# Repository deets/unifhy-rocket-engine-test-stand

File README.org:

* UNIFHY - universeller Prüfstand für Feststoff- und Hybridmotoren

Ziel dieses Projektes ist die Entwicklung eines preiswerten
Prüfstandes mit einem Preis von maximal 500 EUR.

Der Prüfstand besteht aus drei Modulen:

 - Modul 1: einem aus ITEM Prüfbalken bestehenden mechanischen Aufbau.
 - Modul 2: einer Prüfbox zur Datenaufnahme, Speicherung, Übermittlung und
   gegebenenfalls Fernsteuerung.
 - Modul 3: einer Software zur Konfiguration, Datenerfassung und Auswertung von Modul 2.

Hier die [[file:doc/Pruefstand_UNIFHY.pdf][Anforderungen erhoben am 22.02.2020]].

** Modul 1 - Teststand

Ein Aufbau des Testands von Andreas:

[[./doc/Teststand-Totale.jpg]]

[[./doc/Hybrid-Haengend.jpg]]

[[./doc/Test-mit-laufendem-Motor.jpg]]

** Modul 2 - Firmware

*** ADS1256 Breakout Board

Pin out of the breakout board as seen from top with control interface
to the left:

|-----+----------+---------|
| Pin | Function | P2 Eval |
|-----+----------+---------|
|   1 | PDWN     |      21 |
|   2 | CS_      |      20 |
|   3 | DRDY     |      19 |
|   4 | DOUT     |      17 |
|   5 | DIN      |      18 |
|   6 | SCLK     |      16 |
|   7 | GND      |     GND |
|   8 | 5V       |     EXT |
|-----+----------+---------|

#+attr_html: :width 400 px
[[file:doc/ads1256-breakout.jpg]]

** GIT Konfiguration

Wir arbeiten mit einem [[https://medium.com/singlestone/a-git-workflow-using-rebase-1b1210de83e5][rebase]] basierten GIT workflow. Dazu ist es
hilfreich eine Reihe von Einstellungen vorzunehmen. Die folgenden
Kommandos werden in einer Shell eingegeben, und man muss sich in
der Arbeitskopie befinden:

#+begin_src bash
git config pull.rebase true
#+end_src

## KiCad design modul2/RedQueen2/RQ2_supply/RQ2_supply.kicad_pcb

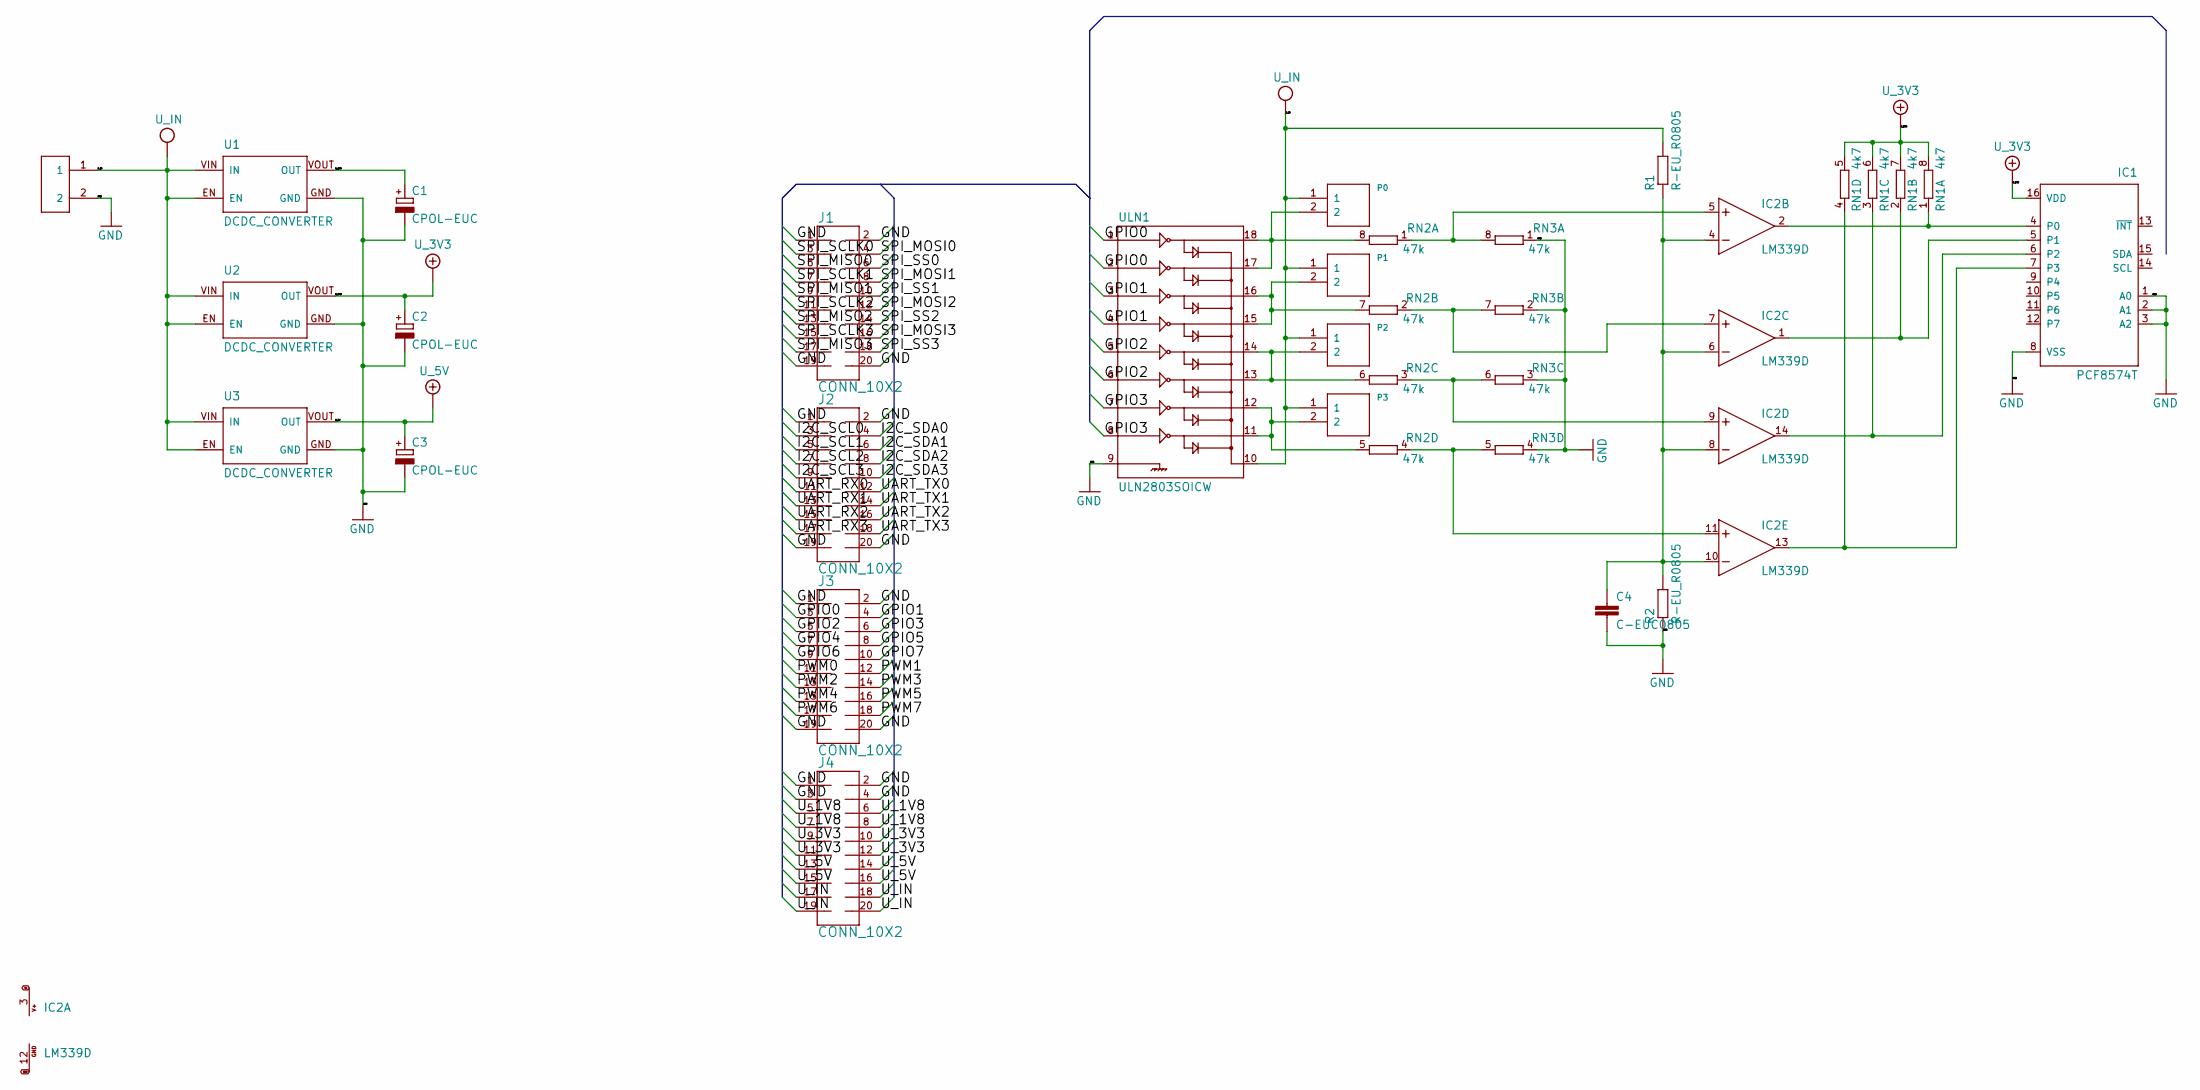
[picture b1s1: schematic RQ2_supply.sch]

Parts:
C1, C2, C3: CPOL-EUC; PANASONIC_C
C4: C-EUC0805; C0805
IC1: PCF8574T; SO16W
IC2: LM339D; SO14
J1, J2, J3, J4: CONN_10X2; 2X10
P0, P1, P2, P3: 2PIN; B2B-PH-K-S
R1, R2: R-EU_R0805; R0805
RN1: 4k7; 0603-ARV
RN2, RN3: 47k; 0603-ARV
U1, U2, U3: DCDC_CONVERTER
U$1: XT_CONN; XT30_PCB
ULN1: ULN2803SOICW; SO18L

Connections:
/GPIO0: J3.3, ULN1.1, ULN1.2
/GPIO1: J3.4, ULN1.3, ULN1.4
/GPIO2: J3.5, ULN1.5, ULN1.6
/GPIO3: J3.6, ULN1.7, ULN1.8
/GPIO4: J3.7
/GPIO5: J3.8
/GPIO6: J3.9
/GPIO7: J3.10
/I2C_SCL0: J2.3
/I2C_SCL1: J2.5
/I2C_SCL2: J2.7
/I2C_SCL3: J2.9
/I2C_SDA0: J2.4
/I2C_SDA1: J2.6
/I2C_SDA2: J2.8
/I2C_SDA3: J2.10
/PWM0: J3.11
/PWM1: J3.12
/PWM2: J3.13
/PWM3: J3.14
/PWM4: J3.15
/PWM5: J3.16
/PWM6: J3.17
/PWM7: J3.18
/SPI_MISO0: J1.5
/SPI_MISO1: J1.9
/SPI_MISO2: J1.13
/SPI_MISO3: J1.17
/SPI_MOSI0: J1.4
/SPI_MOSI1: J1.8
/SPI_MOSI2: J1.12
/SPI_MOSI3: J1.16
/SPI_SCLK0: J1.3
/SPI_SCLK1: J1.7
/SPI_SCLK2: J1.11
/SPI_SCLK3: J1.15
/SPI_SS0: J1.6
/SPI_SS1: J1.10
/SPI_SS2: J1.14
/SPI_SS3: J1.18
/UART_RX0: J2.11
/UART_RX1: J2.13
/UART_RX2: J2.15
/UART_RX3: J2.17
/UART_TX0: J2.12
/UART_TX1: J2.14
/UART_TX2: J2.16
/UART_TX3: J2.18
/U_1V8: C1.+, J4.5, J4.6, J4.7, J4.8, U1.VOUT (OUT)
GND: C1.-, C2.-, C3.-, C4.2, IC1.1 (A0), IC1.2 (A1), IC1.3 (A2), IC1.8 (VSS), IC2.12 (GND), J1.1, J1.2, J1.19, J1.20, J2.1, J2.2, J2.19, J2.20, J3.1, J3.2, J3.19, J3.20, J4.1, J4.2, J4.3, J4.4, R2.1, RN3.1, RN3.2 (1), RN3.3 (1), RN3.4 (1), U1.GND, U2.GND, U3.GND, U$1.2, ULN1.9
unnamed: C4.1, IC2.4 (-IN), IC2.6 (-IN), IC2.8 (-IN), IC2.10 (-IN), R1.1, R2.2
unnamed: IC1.4 (P0), IC2.2 (OUT), RN1.1
unnamed: IC1.5 (P1), IC2.1 (OUT), RN1.2 (1)
unnamed: IC1.6 (P2), IC2.14 (OUT), RN1.3 (1)
unnamed: IC1.7 (P3), IC2.13 (OUT), RN1.4 (1)
unnamed: IC2.5 (+IN), RN2.1, RN3.8 (2)
unnamed: IC2.7 (+IN), RN2.2 (1), RN3.7 (2)
unnamed: IC2.9 (+IN), RN2.3 (1), RN3.6 (2)
unnamed: IC2.11 (+IN), RN2.4 (1), RN3.5 (2)
unnamed: P0.2, RN2.8 (2), ULN1.17, ULN1.18
unnamed: P1.2, RN2.7 (2), ULN1.15, ULN1.16
unnamed: P2.2, RN2.6 (2), ULN1.13, ULN1.14
unnamed: P3.2, RN2.5 (2), ULN1.11, ULN1.12
U_3V3: C2.+, IC1.16 (VDD), J4.9, J4.10, J4.11, J4.12, RN1.5 (2), RN1.6 (2), RN1.7 (2), RN1.8 (2), U2.VOUT (OUT)
U_5V: C3.+, J4.13, J4.14, J4.15, J4.16, U3.VOUT (OUT)
U_IN: J4.17, J4.18, J4.19, J4.20, P0.1, P1.1, P2.1, P3.1, R1.2, U1.EN, U1.VIN (IN), U2.EN, U2.VIN (IN), U3.EN, U3.VIN (IN), U$1.1, ULN1.10
V+: IC2.3 (V+)

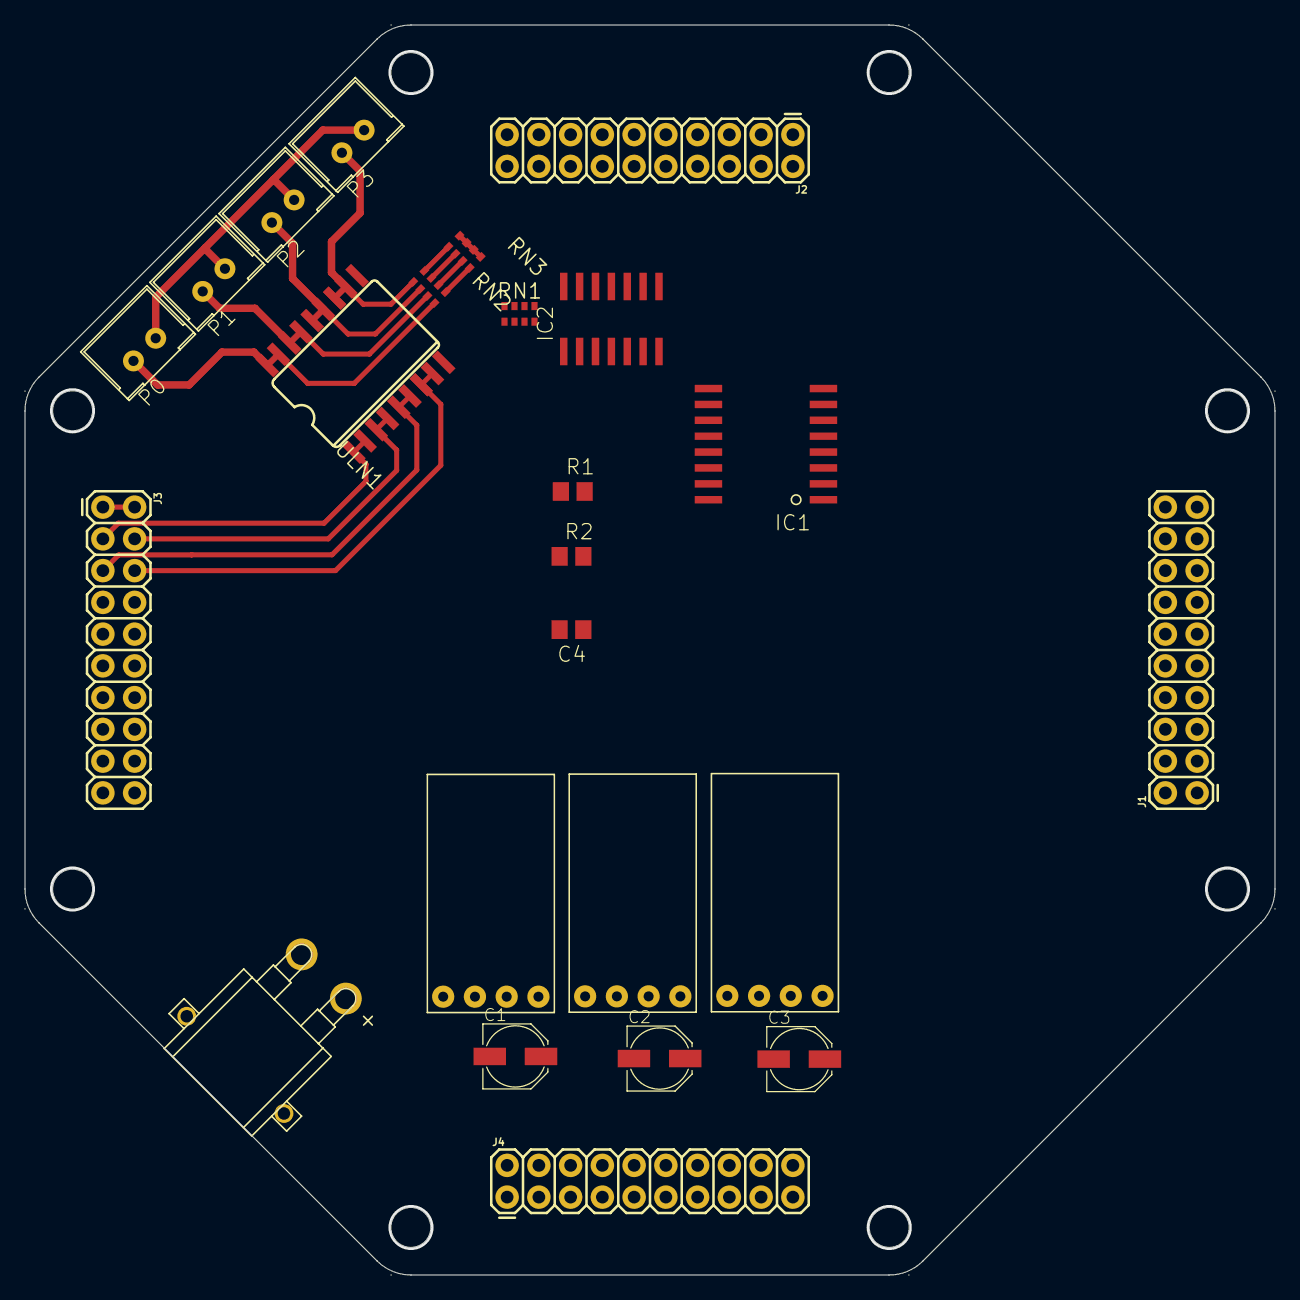
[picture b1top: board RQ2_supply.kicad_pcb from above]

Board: 2 copper layers, 100.0 x 100.0 mm, 24 parts (0 on the bottom side), 22 nets.

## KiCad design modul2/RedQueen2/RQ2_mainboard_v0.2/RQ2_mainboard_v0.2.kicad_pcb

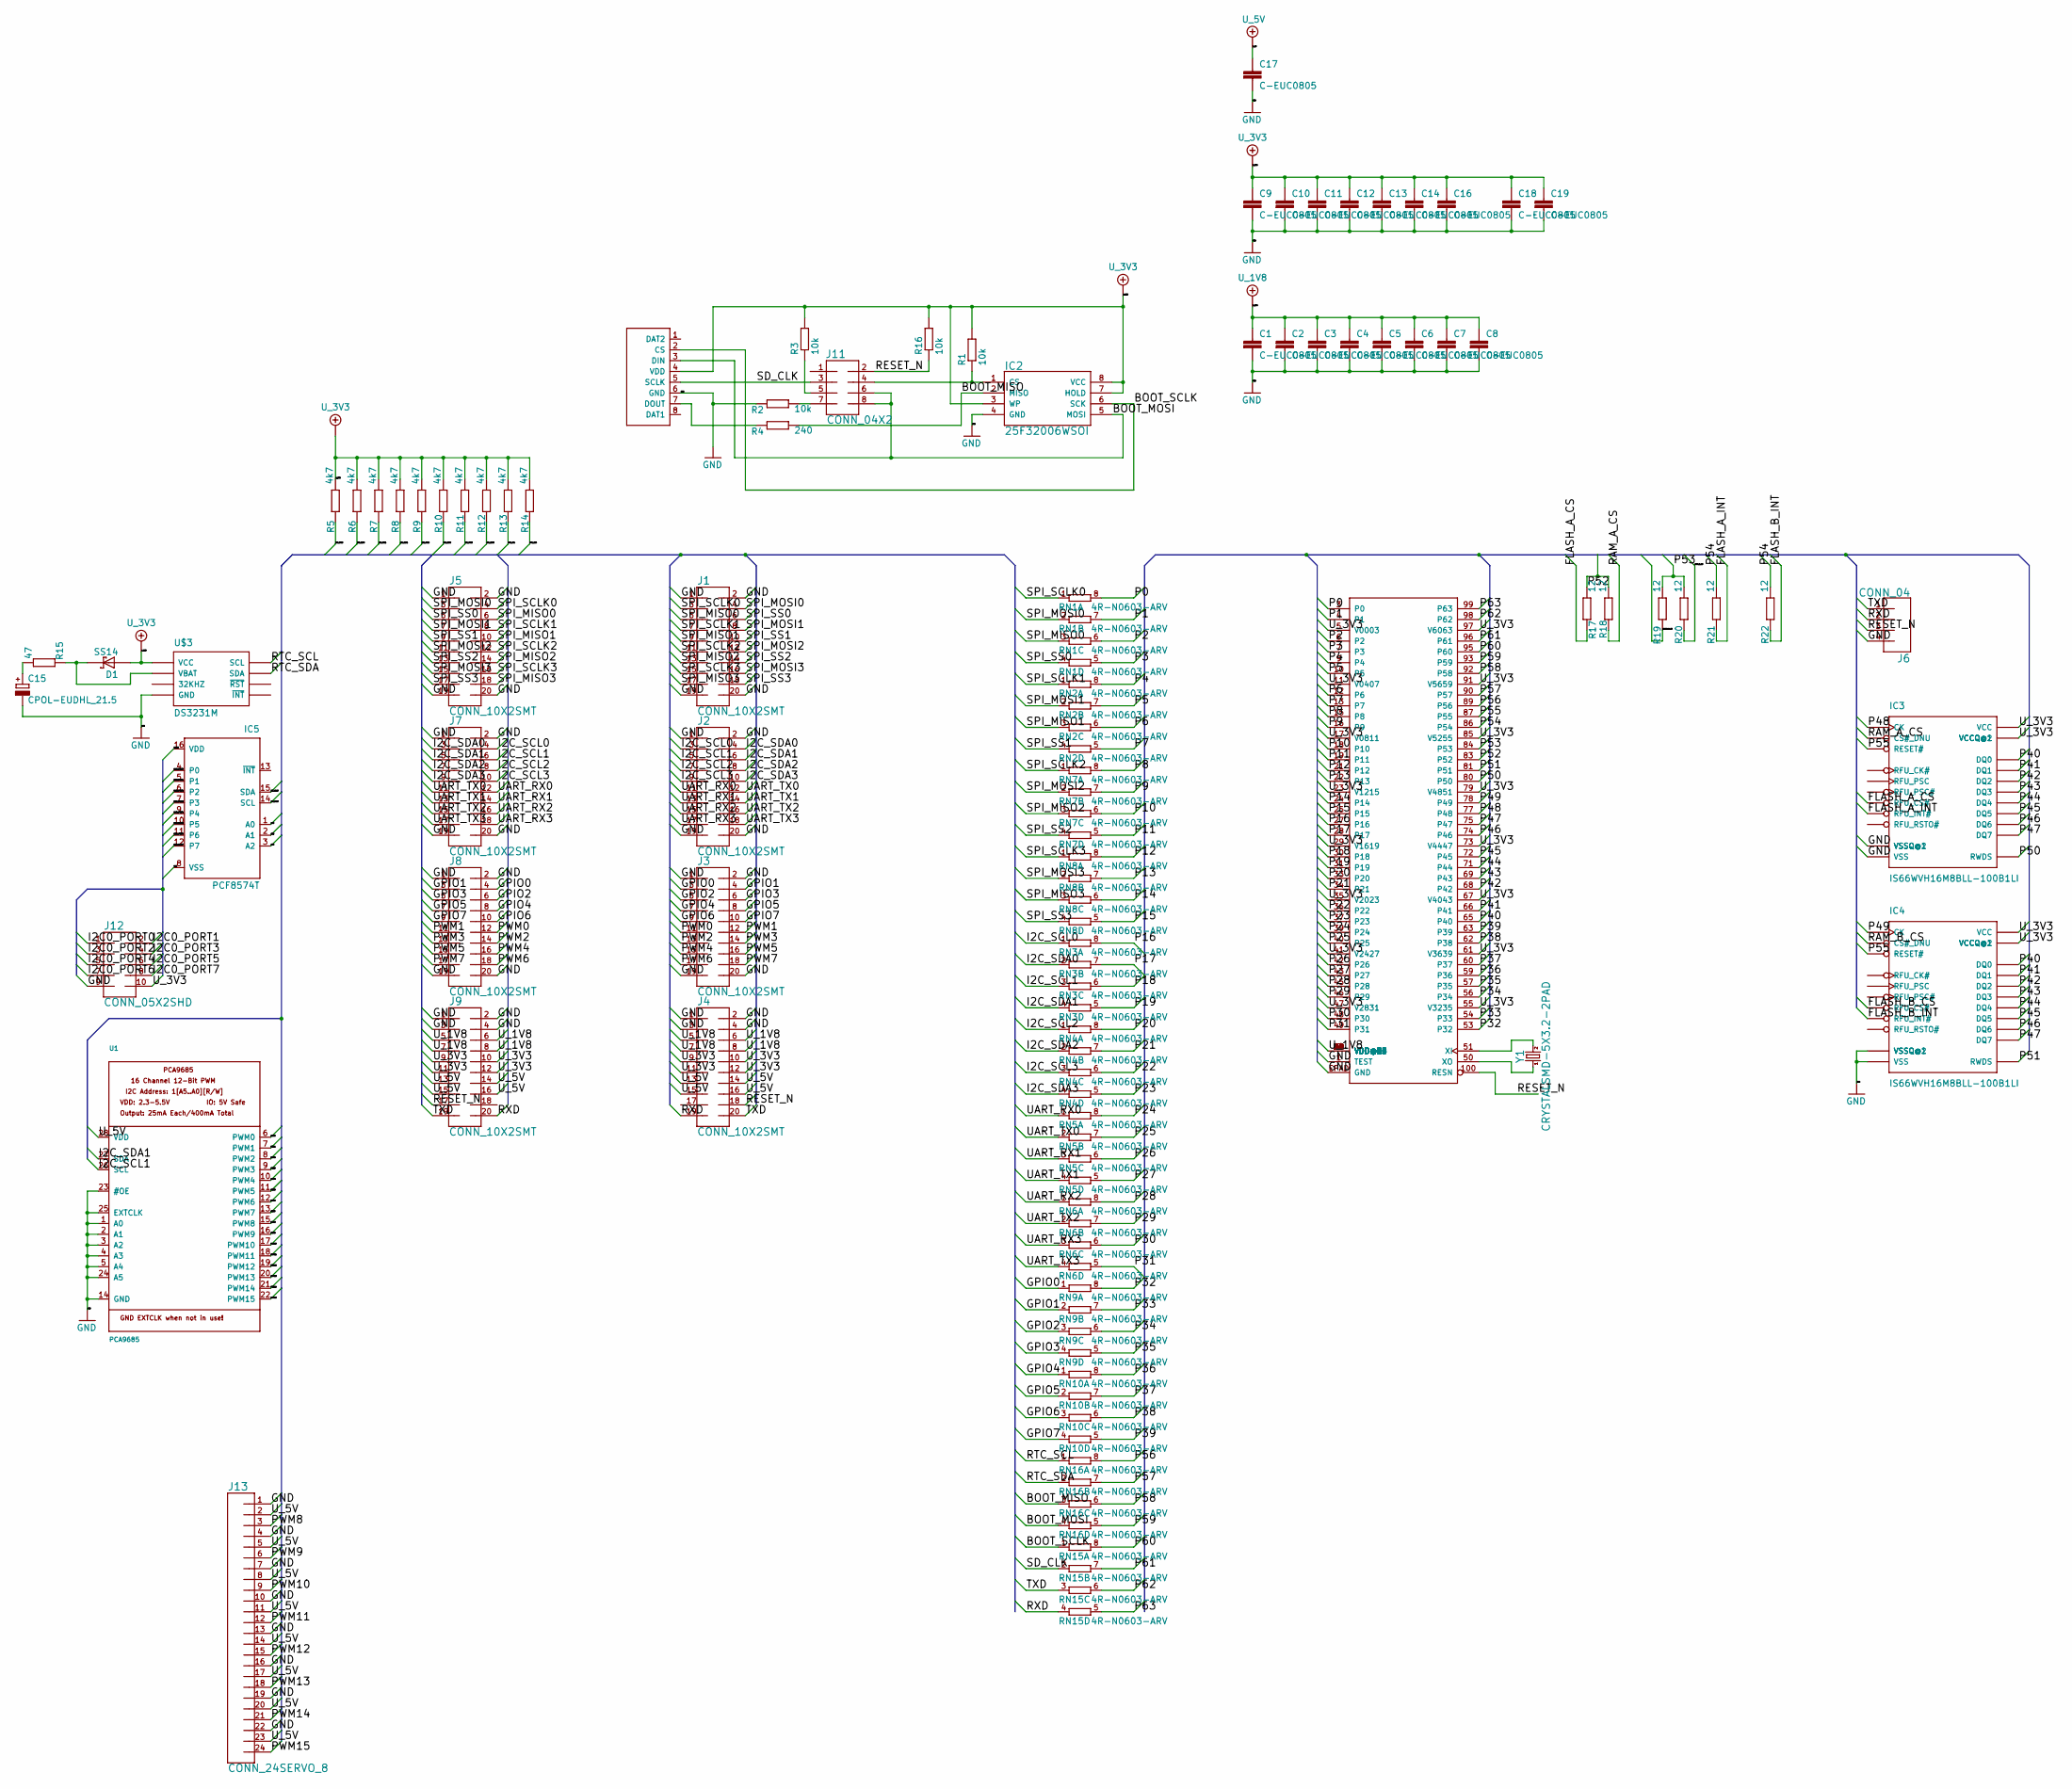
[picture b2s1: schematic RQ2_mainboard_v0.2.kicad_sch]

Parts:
C1, C2, C3, C4, C5, C6, C7, C8, C9, C10, C11, C12, C13, C14, C16, C17, C18, C19: C-EUC0805; C0805
C15: CPOL-EUDHL_21.5; DHL_21.5
D1: SS14; SMA_403D
IC1: P2X8C4M64P; TQFP100
IC2: 25F32006WSOI; SO08-EIAJ
IC3, IC4: IS66WVH16M8BLL-100B1LI; BGA-24
IC5: PCF8574T; SO16W
J1, J2, J3, J4, J5, J7, J8, J9: CONN_10X2SMT; 2X10_SMT
J6: CONN_04; 1X04
J11: CONN_04X2; 2X4
J12: CONN_05X2SHD; 2X5-SHROUDED
J13: CONN_24SERVO_8; 3X8
R1, R2, R3, R16: 10k; R0603
R4: 240; R0603
R5, R6, R7, R8, R9, R10, R11, R12, R13, R14: 4k7; R0603
R15: 47; R0603
R17, R18, R19, R20, R21, R22: 12; R0402
RN1, RN2, RN3, RN4, RN5, RN6, RN7, RN8, RN9, RN10, RN15, RN16: 4R-N0603-ARV; 0603-ARV
U1: PCA9685; TSSOP28
U$2: MICRO_SD_CONNECTORMOLEX_HINGE; MICRO_SD
U$3: DS3231M; SO-8
Y1: CRYSTALSMD-5X3.2-2PAD; CRYSTAL-SMD-5X3.2-2PAD

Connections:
/BOOT_MISO: IC2.2 (MISO), R4.1, RN16.3 (1)
/BOOT_MOSI: IC2.5 (MOSI), J11.6, J11.8, RN16.4 (1), U$2.3 (DIN)
/BOOT_SCLK: IC2.6 (SCK), RN15.1, U$2.2 (CS)
/FLASH_A_CS: IC3.C2 (RFU_CS#), R17.2
/FLASH_A_INT: IC3.A5 (RFU_INT#), R21.2
/FLASH_B_CS: IC4.C2 (RFU_CS#), R19.2
/FLASH_B_INT: IC4.A5 (RFU_INT#), R22.2
/GPIO0: J3.3, J8.4, RN9.1
/GPIO1: J3.4, J8.3, RN9.2 (1)
/GPIO2: J3.5, J8.6, RN9.3 (1)
/GPIO3: J3.6, J8.5, RN9.4 (1)
/GPIO4: J3.7, J8.8, RN10.1
/GPIO5: J3.8, J8.7, RN10.2 (1)
/GPIO6: J3.9, J8.10, RN10.3 (1)
/GPIO7: J3.10, J8.9, RN10.4 (1)
/I2C0_PORT0: IC5.4 (P0), J12.1
/I2C0_PORT1: IC5.5 (P1), J12.2
/I2C0_PORT2: IC5.6 (P2), J12.3
/I2C0_PORT3: IC5.7 (P3), J12.4
/I2C0_PORT4: IC5.9 (P4), J12.5
/I2C0_PORT5: IC5.10 (P5), J12.6
/I2C0_PORT6: IC5.11 (P6), J12.7
/I2C0_PORT7: IC5.12 (P7), J12.8
/I2C_SCL0: IC5.14 (SCL), J2.3, J7.4, R5.1, RN3.1
/I2C_SCL1: J2.5, J7.6, R7.1, RN3.3 (1), U1.26 (SCL)
/I2C_SCL2: J2.7, J7.8, R9.1, RN4.1
/I2C_SCL3: J2.9, J7.10, R11.1, RN4.3 (1)
/I2C_SDA0: IC5.15 (SDA), J2.4, J7.3, R6.1, RN3.2 (1)
/I2C_SDA1: J2.6, J7.5, R8.1, RN3.4 (1), U1.27 (SDA)
/I2C_SDA2: J2.8, J7.7, R10.1, RN4.2 (1)
/I2C_SDA3: J2.10, J7.9, R12.1, RN4.4 (1)
/P0: IC1.3 (P0), RN1.8 (2)
/P1: IC1.4 (P1), RN1.7 (2)
/P2: IC1.6 (P2), RN1.6 (2)
/P3: IC1.7 (P3), RN1.5 (2)
/P4: IC1.9 (P4), RN2.8 (2)
/P5: IC1.10 (P5), RN2.7 (2)
/P6: IC1.12 (P6), RN2.6 (2)
/P7: IC1.13 (P7), RN2.5 (2)
/P8: IC1.15 (P8), RN7.8 (2)
/P9: IC1.16 (P9), RN7.7 (2)
/P10: IC1.18 (P10), RN7.6 (2)
/P11: IC1.19 (P11), RN7.5 (2)
/P12: IC1.21 (P12), RN8.8 (2)
/P13: IC1.22 (P13), RN8.7 (2)
/P14: IC1.24 (P14), RN8.6 (2)
/P15: IC1.25 (P15), RN8.5 (2)
/P16: IC1.27 (P16), RN3.8 (2)
/P17: IC1.28 (P17), RN3.7 (2)
/P18: IC1.30 (P18), RN3.6 (2)
/P19: IC1.31 (P19), RN3.5 (2)
/P20: IC1.33 (P20), RN4.8 (2)
/P21: IC1.34 (P21), RN4.7 (2)
/P22: IC1.36 (P22), RN4.6 (2)
/P23: IC1.37 (P23), RN4.5 (2)
/P24: IC1.39 (P24), RN5.8 (2)
/P25: IC1.40 (P25), RN5.7 (2)
/P26: IC1.42 (P26), RN5.6 (2)
/P27: IC1.43 (P27), RN5.5 (2)
/P28: IC1.45 (P28), RN6.8 (2)
/P29: IC1.46 (P29), RN6.7 (2)
/P30: IC1.48 (P30), RN6.6 (2)
/P31: IC1.49 (P31), RN6.5 (2)
/P32: IC1.53 (P32), RN9.8 (2)
/P33: IC1.54 (P33), RN9.7 (2)
/P34: IC1.56 (P34), RN9.6 (2)
/P35: IC1.57 (P35), RN9.5 (2)
/P36: IC1.59 (P36), RN10.8 (2)
/P37: IC1.60 (P37), RN10.7 (2)
/P38: IC1.62 (P38), RN10.6 (2)
/P39: IC1.63 (P39), RN10.5 (2)
/P40: IC1.65 (P40), IC3.D3 (DQ0), IC4.D3 (DQ0)
/P41: IC1.66 (P41), IC3.D2 (DQ1), IC4.D2 (DQ1)
/P42: IC1.68 (P42), IC3.C4 (DQ2), IC4.C4 (DQ2)
/P43: IC1.69 (P43), IC3.D4 (DQ3), IC4.D4 (DQ3)
/P44: IC1.71 (P44), IC3.D5 (DQ4), IC4.D5 (DQ4)
/P45: IC1.72 (P45), IC3.E3 (DQ5), IC4.E3 (DQ5)
/P46: IC1.74 (P46), IC3.E2 (DQ6), IC4.E2 (DQ6)
/P47: IC1.75 (P47), IC3.E1 (DQ7), IC4.E1 (DQ7)
/P48: IC1.77 (P48), IC3.B2 (CK)
/P49: IC1.78 (P49), IC4.B2 (CK)
/P50: IC1.80 (P50), IC3.C3 (RWDS)
/P51: IC1.81 (P51), IC4.C3 (RWDS)
/P52: IC1.83 (P52), R17.1, R18.1
/P53: IC1.84 (P53), R19.1, R20.1
/P54: IC1.86 (P54), R21.1, R22.1
/P55: IC1.87 (P55), IC3.A4 (RESET#), IC4.A4 (RESET#)
/P56: IC1.89 (P56), RN16.8 (2)
/P57: IC1.90 (P57), RN16.7 (2)
/P58: IC1.92 (P58), RN16.6 (2)
/P59: IC1.93 (P59), RN16.5 (2)
/P60: IC1.95 (P60), RN15.8 (2)
/P61: IC1.96 (P61), RN15.7 (2)
/P62: IC1.98 (P62), RN15.6 (2)
/P63: IC1.99 (P63), RN15.5 (2)
/PWM0: J3.11, J8.12, U1.6 (PWM0)
/PWM1: J3.12, J8.11, U1.7 (PWM1)
/PWM2: J3.13, J8.14, U1.8 (PWM2)
/PWM3: J3.14, J8.13, U1.9 (PWM3)
/PWM4: J3.15, J8.16, U1.10 (PWM4)
/PWM5: J3.16, J8.15, U1.11 (PWM5)
/PWM6: J3.17, J8.18, U1.12 (PWM6)
/PWM7: J3.18, J8.17, U1.13 (PWM7)
/PWM8: J13.3, U1.15 (PWM8)
/PWM9: J13.6, U1.16 (PWM9)
/PWM10: J13.9, U1.17 (PWM10)
/PWM11: J13.12, U1.18 (PWM11)
/PWM12: J13.15, U1.19 (PWM12)
/PWM13: J13.18, U1.20 (PWM13)
/PWM14: J13.21, U1.21 (PWM14)
/PWM15: J13.24, U1.22 (PWM15)
/RAM_A_CS: IC3.A3 (CS#_DNU), R18.2
/RAM_B_CS: IC4.A3 (CS#_DNU), R20.2
/RESET_N: IC1.100 (RESN), J4.18, J6.3, J9.17, J11.2, R16.1
/RTC_SCL: R13.1, RN16.1, U$3.8 (SCL)
/RTC_SDA: R14.1, RN16.2 (1), U$3.7 (SDA)
/RXD: J4.19, J6.2, J9.20, RN15.4 (1)
/SD_CLK: J11.3, RN15.2 (1), U$2.5 (SCLK)
/SPI_MISO0: J1.5, J5.6, RN1.3 (1)
/SPI_MISO1: J1.9, J5.10, RN2.3 (1)
/SPI_MISO2: J1.13, J5.14, RN7.3 (1)
/SPI_MISO3: J1.17, J5.18, RN8.3 (1)
/SPI_MOSI0: J1.4, J5.3, RN1.2 (1)
/SPI_MOSI1: J1.8, J5.7, RN2.2 (1)
/SPI_MOSI2: J1.12, J5.11, RN7.2 (1)
/SPI_MOSI3: J1.16, J5.15, RN8.2 (1)
/SPI_SCLK0: J1.3, J5.4, RN1.1
/SPI_SCLK1: J1.7, J5.8, RN2.1
/SPI_SCLK2: J1.11, J5.12, RN7.1
/SPI_SCLK3: J1.15, J5.16, RN8.1
/SPI_SS0: J1.6, J5.5, RN1.4 (1)
/SPI_SS1: J1.10, J5.9, RN2.4 (1)
/SPI_SS2: J1.14, J5.13, RN7.4 (1)
/SPI_SS3: J1.18, J5.17, RN8.4 (1)
/TXD: J4.20, J6.1, J9.19, RN15.3 (1)
/UART_RX0: J2.11, J7.12, RN5.1
/UART_RX1: J2.13, J7.14, RN5.3 (1)
/UART_RX2: J2.15, J7.16, RN6.1
/UART_RX3: J2.17, J7.18, RN6.3 (1)
/UART_TX0: J2.12, J7.11, RN5.2 (1)
/UART_TX1: J2.14, J7.13, RN5.4 (1)
/UART_TX2: J2.16, J7.15, RN6.2 (1)
/UART_TX3: J2.18, J7.17, RN6.4 (1)
GND: C1.2, C2.2, C3.2, C4.2, C5.2, C6.2, C7.2, C8.2, C9.2, C10.2, C11.2, C12.2, C13.2, C14.2, C15.-, C16.2, C17.2, C18.2, C19.2, IC1.1 (TEST), IC1.EPAD (GND), IC2.4 (GND), IC3.B3 (VSS), IC3.C1 (VSSQ@1), IC3.E5 (VSSQ@2), IC4.B3 (VSS), IC4.C1 (VSSQ@1), IC4.E5 (VSSQ@2), IC5.1 (A0), IC5.2 (A1), IC5.3 (A2), IC5.8 (VSS), J1.1, J1.2, J1.19, J1.20, J2.1, J2.2, J2.19, J2.20, J3.1, J3.2, J3.19, J3.20, J4.1, J4.2, J4.3, J4.4, J5.1, J5.2, J5.19, J5.20, J6.4, J7.1, J7.2, J7.19, J7.20, J8.1, J8.2, J8.19, J8.20, J9.1, J9.2, J9.3, J9.4, J12.9, J13.1, J13.4, J13.7, J13.10, J13.13, J13.16, J13.19, J13.22, R2.2, U1.1 (A0), U1.2 (A1), U1.3 (A2), U1.4 (A3), U1.5 (A4), U1.14 (GND), U1.23 (#OE), U1.24 (A5), U1.25 (EXTCLK), U$2.6 (GND), U$3.5 (GND)
unnamed: C15.+, R15.2
unnamed: D1.C, R15.1, U$3.6 (VBAT)
unnamed: IC1.50 (XO), Y1.P$1 (1)
unnamed: IC1.51 (XI), Y1.P$2 (2)
unnamed: IC2.1 (CS), J11.4, R1.1
unnamed: J11.5, R3.1
unnamed: J11.7, R2.1
unnamed: R4.2, U$2.7 (DOUT)
U_1V8: C1.1, C2.1, C3.1, C4.1, C5.1, C6.1, C7.1, C8.1, IC1.2 (VDD@1), IC1.8 (VDD@2), IC1.14 (VDD@3), IC1.20 (VDD@4), IC1.26 (VDD@5), IC1.32 (VDD@6), IC1.38 (VDD@7), IC1.44 (VDD@8), IC1.52 (VDD@9), IC1.58 (VDD@10), IC1.64 (VDD@11), IC1.70 (VDD@12), IC1.76 (VDD@13), IC1.82 (VDD@14), IC1.88 (VDD@15), IC1.94 (VDD@16), J4.5, J4.6, J4.7, J4.8, J9.5, J9.6, J9.7, J9.8
U_3V3: C9.1, C10.1, C11.1, C12.1, C13.1, C14.1, C16.1, C18.1, C19.1, D1.A, IC1.5 (V0003), IC1.11 (V0407), IC1.17 (V0811), IC1.23 (V1215), IC1.29 (V1619), IC1.35 (V2023), IC1.41 (V2427), IC1.47 (V2831), IC1.55 (V3235), IC1.61 (V3639), IC1.67 (V4043), IC1.73 (V4447), IC1.79 (V4851), IC1.85 (V5255), IC1.91 (V5659), IC1.97 (V6063), IC2.3 (WP), IC2.7 (HOLD), IC2.8 (VCC), IC3.B4 (VCC), IC3.D1 (VCCQ@1), IC3.E4 (VCCQ@2), IC4.B4 (VCC), IC4.D1 (VCCQ@1), IC4.E4 (VCCQ@2), IC5.16 (VDD), J4.9, J4.10, J4.11, J4.12, J9.9, J9.10, J9.11, J9.12, J12.10, R1.2, R3.2, R5.2, R6.2, R7.2, R8.2, R9.2, R10.2, R11.2, R12.2, R13.2, R14.2, R16.2, U$2.4 (VDD), U$3.2 (VCC)
U_5V: C17.1, J4.13, J4.14, J4.15, J4.16, J9.13, J9.14, J9.15, J9.16, J13.2, J13.5, J13.8, J13.11, J13.14, J13.17, J13.20, J13.23, U1.28 (VDD)

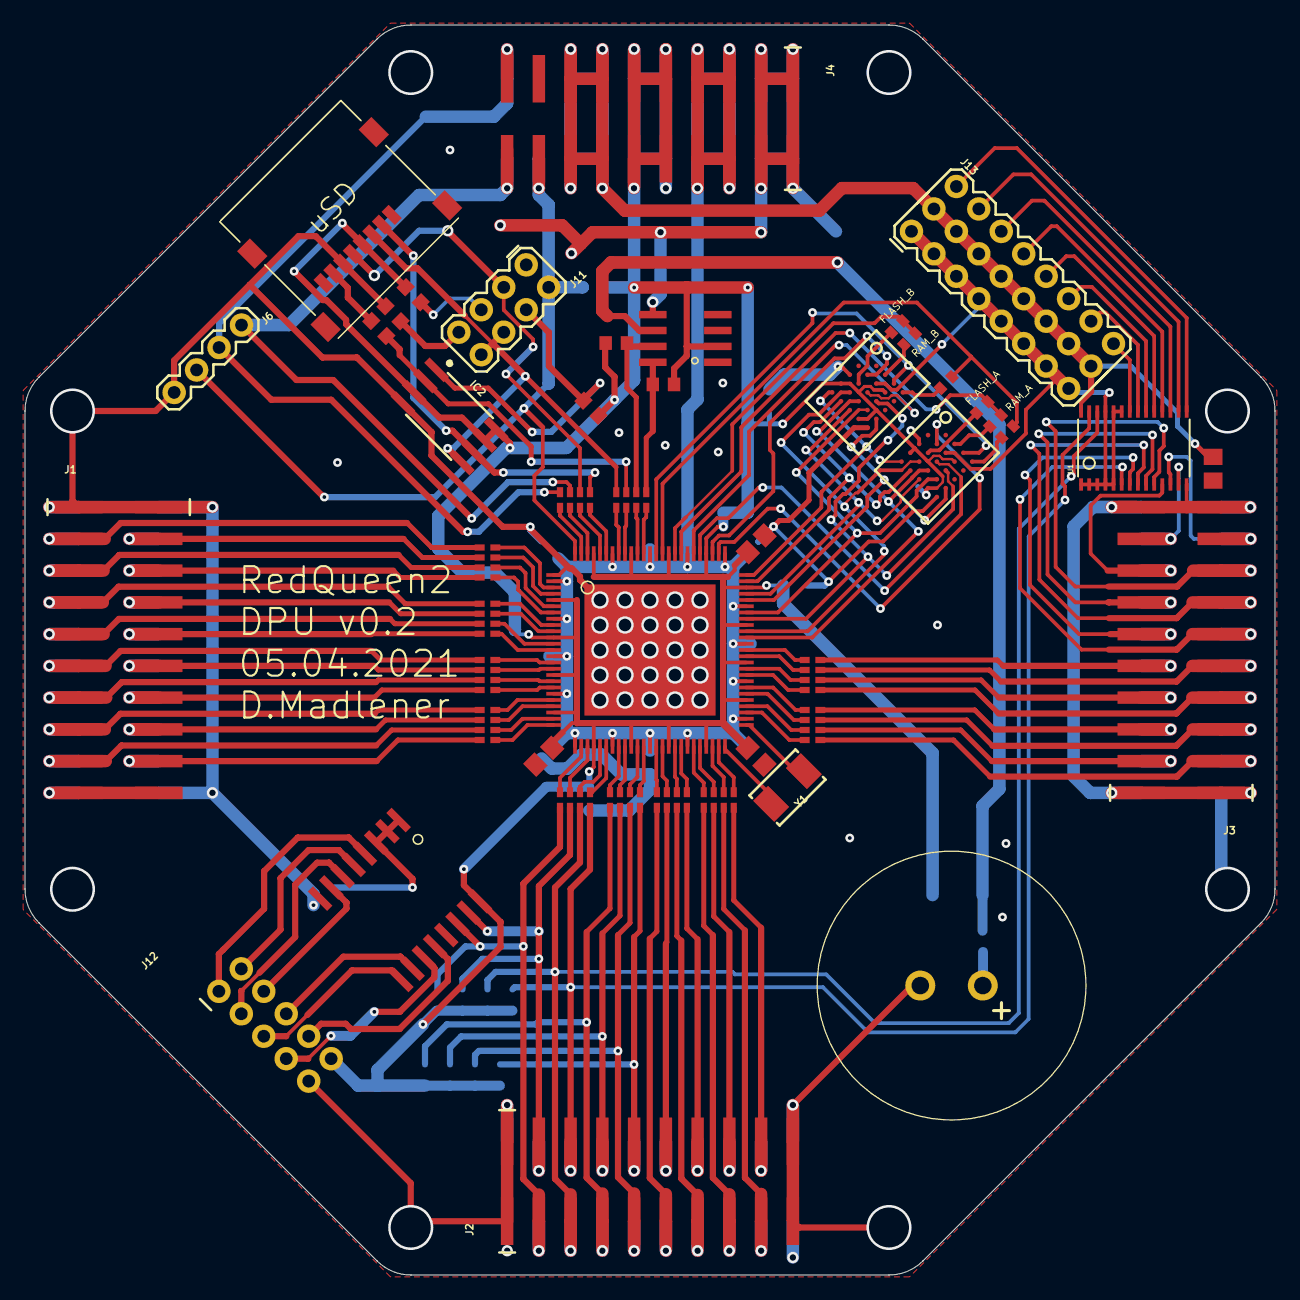
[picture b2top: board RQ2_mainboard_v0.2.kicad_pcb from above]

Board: 2 copper layers, 100.0 x 100.0 mm, 75 parts (0 on the bottom side), 155 nets.

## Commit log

2020-02-29 Introduce ringbuffer class
2020-02-29 Add arduino layer as component
2020-02-29 Initial commit - 500us loop with 9 long words SPI communication
2020-02-29 Dynamic period to wait when sampling
2020-02-29 Introduce data-logger and signal sampler task
2020-02-29 Convert data sampler into class
2020-02-29 Renamed task
2020-02-29 Add WIFI to the mix
    Also use polling transactions & retry to mount the SD-Card
    Wifi deteriorates the SPI task timing. Will have to investigate.
2020-02-29 Set up SD-card reading
2020-02-29 Switch to different SPI channel and hardware CS
2020-02-29 Add a tiny description
2020-02-29 Enhance datalogger to write strings using ADL
2020-06-01 Implement DataLogger as Task
2020-06-01 Move ESP32 test balloon into own subdirectory
2020-06-05 Erste Schritte Dokumentation
2020-06-10 First commit of Modul3 Software
2020-06-10 Etwas GIT Dokumentation
2020-06-10 Datenblatt des ADC
2020-06-21 Add some images
2020-08-05 Add WIFI to the mix
2020-08-05 Moved to modul2 subfolder
2020-08-05 Upgrade to IDF 3.3.2
2020-09-29 RQ2 commit #1
    New Eagle boards and schematics, RedQueen 2 mainboard and supply
2021-03-05 Add some documentation about the ADS1256 breakout board
2021-03-05 P2 hello world with extra serial
    The extra serial is because I currently can't flash but only load to
    memory.
2021-03-07 Began implementing ADS1256 in spin2
    So far only the physical setup is mimicked and according to the
    logic analyser, the communication looks good.
2021-03-08 Read single channel conversion result
2021-03-08 Cleanup and fix bug in WREG
    It appears one needs to wait for DRDY LOW before a register can be written.
2021-03-13 Implemented buffered interface on top of existing ADS1256 code
2021-03-14 Implement the continuous acquisition mode
2021-03-14 Remove warnings after introducing -Wall
2021-03-21 Working ringbuffer and verified >4K data acquisition speed
2021-03-21 Start working on the RQ serial protocol
2021-03-28 Start work on serial protocol
2021-03-28 Ignore build-directory
2021-03-28 Improve documentation a bit
2021-03-28 Implement first command: P for PING, returns a P for PONG
2021-05-30 First introduction of SD-Card/FAT32 code
2021-05-30 Implement the R command
    This allows to set the samplerate
2021-05-30 Beginnings of the continuous acquisition
2021-05-30 Implement thinning
2021-05-30 Continuous data acquisition should work now
2021-05-30 Add P2 Eval Board schematic
2021-06-04 Move to colons vs dollarsigns as separators, as suggested by David
2021-06-04 Introduce the SD Writer and figure out the index of the next file to create
2021-06-04 Introduce cmd architecture and create new file
2021-06-05 Refactor: introduce util object and use it throughout
2021-06-05 Cleanup: docstring
2021-06-05 Signify the synchronous nature of the begin call
2021-06-05 Basic SD card writing works
    Currently the 30K SPS mode does not seem to properly work, but
    we *do* write stuff!
2021-06-09 Pull in dependencies so others can build
2021-06-11 Writing of data works at full speed
2021-06-11 Smaller ringbuffer, seems still to be enough
2021-06-13 Remove audio DAC code
2021-06-18 Pull startswith/endswith into util and add timediff
2021-06-18 Increase clkfreq to 300_000_000
2021-06-18 Fix linesize and report SD card status via LED
2021-06-18 Remove dead/unused code
2021-06-18 Never allow timestamp 0 so we can use it as sentinel value
2021-06-18 DROPME: Mark block-writing with pin
2021-06-19 Flush after one sector
2021-06-19 Communicate run statistics and write it as last line
2021-06-19 Introduce a running-flag to allow for non-sd-card operation
2021-06-19 Introduce reps and duration and a statistics call as finalization
2021-06-19 Gather statistics during the run and offer them via S-command
2021-06-19 Seed the avg_timediff with a value based on the actual data rate
2021-06-19 Re-organize code so that obtaining the expected timediff works
2021-06-20 Start Connector Implementation
2021-06-20 Implement listing files
2021-06-20 Align debugging statement output with last file line order
2021-06-20 Add size to file listing
2021-06-20 Refactor: improve rq_finalize, no argument anymore
2021-06-20 Implement streaming files via serial line
2021-06-20 Start to implement proper interface for starting/stopping of data acquistion
2021-06-26 Make sdwriter take callbacks to the ringbuffer
    This allows for easy swapping of the ringbuffer implementation
2021-06-26 Move up to 1_000_000 BPS for serial communication
2021-06-26 Trick flexspin code generation to return actual file size
    This removes the need for the debug-mode
2021-06-27 Replace ringbuffer with hyper_ringbuffer
2021-06-27 Improve sdwriter
    This includes a rather ugly workaround for the WAITATN that
    fails me in the end()-method
2021-06-27 Some changes to the test script
2021-06-27 Some data display script
2021-06-27 Add HyperRAM driver
2021-06-27 Comment out a lot of debug statements
2021-06-27 Apply wuerfel_21 fix that isn't confusing code generation
2021-06-27 Add a HyperRAM ringbuffer implementation
    This includes a test that seems to indicate things are working
2021-07-03 changed variable name to enable compilation with Propeller Tool
2021-07-03 just some minor changes to enable compiling with Propeller Tool
2021-07-04 Fix bug with not waiting for serial streaming to finish
2021-07-04 It seems this is working to write 10 seconds of data
2021-07-04 Removed superfluous terminal commands
2021-07-04 Test pin reading
2021-07-04 Introduce SD card and write to it based on the second button
2021-07-04 Clarify names
2021-07-04 Adding a serial output to stream the data away
    This shows that the data is buffered properly
2021-07-04 Trigger data acquisition by button
2021-07-04 Stream the data file line format over serial
2021-07-04 Remove polluting debug statement
2021-07-04 Don't write the data to the SD-card
    This leads to a situation where the data is broken in the beginning
    (presumably during FAT setup) but then starts to become well-formed
    again.
2021-07-04 Moved to new getct()
2021-07-04 Comment out debug commands
2021-07-04 Enlargen line buffer
2021-07-04 Compute biggest diff also when showing the data
2021-07-04 Added reset call to ringbuffer and use it
2021-07-04 Add a tiny stats functionality to the buffered ADS
    This determines the biggest difference between two consecutive
    values. It serves as sanity check in the data corruption
    investigation.
2021-07-07 Fix bug that left a lingering value in the ringbuffer.
    Now it will always be cleared out at the beginning of a continuous acquisition.
2021-07-08 Upper case filenames
2021-07-08 Move HyperRAM to new base and add a little selftest
2021-07-08 Adapt code to the new base for the accessory boards
2021-07-08 Add a simple "linear" clock that just uses an index instead of timestamps
2021-10-12 Update copyright info
    JonnyMac explicitly expressed his wish to not be affiliated
    with derivatives of his code.
2021-10-12 Introduce configuration object
    This depends on a preprocessor variable to select the target board
2021-10-14 Begin working on switched frontend
2021-10-14 Introduce capturing switch
2021-10-18 Fix some timing constants
2021-10-18 Clearer status names
2021-10-18 Use the MUX-method even for single channel data acquisition
    It might be preferable to use RDATAC instead, but for now
    this seems to work well enough and we are expecting multi channel
    reading anyway
2021-10-18 Implement switched frontend
2021-10-18 Intorduce and use convenience method to set the samplerate
    Also improve flashtime by making the ADC buffer smaller - it
    was inflated during debugging.
2021-10-18 Fall out of capturing when the capacity is exhausted
2021-10-24 Refactor status and account for the two cogs driving it.
2022-01-02 Begin cleanup of SD card driver
2022-01-02 wip: debug pin to signify the start of the driver
2022-01-02 Spin2 frontend for sd card cleanup
2022-01-02 Unify handling of R3/R7 responses (R1 + 4 bytes)
2022-01-03 multi blocks beginning
2022-01-30 Move toward ESP SDK 4.2 in an attempt to get faster SD card writes
2022-02-06 Write block-wise to the SD-card
2022-02-12 Enhance sd card writing code based on my ESP32 investigation
2022-02-12 Lower SD-card frequency for better analysis with my logic analyser
2022-02-12 Write based on button-press for simple recording workflow
2022-02-12 Renamed and use parameter for bitwait
2022-02-20 Add KiCad project from mainboard
2022-02-20 Add supply board
2022-03-29 Update (C) notice
2022-03-29 Comment about maximum SPI speed on P2 Eval Rev C
2022-03-29 Prefix SD Card commands for clarity and name collision avoidance
2022-03-29 Remove DEBUG_PIN
2022-03-29 Consistent method names
2022-03-29 Remove superfluous variable
2022-03-29 Add UNIFHY configuration
2022-03-29 Clarified mount code
2022-03-29 Modify frontend to allow for a range of commands
2022-03-29 Pass speed as argument
2022-03-29 Hook my SD SPI code into FAT32
2022-03-30 Fix mountPartition to do what it promises to do and use it
2022-03-30 Introduce l command to list the SD card contents
2022-03-31 Fix FAT32 to conform to the openFile protocol as stated
    Before it would return the filename *or* error string, making
    that hard to decide.
2022-03-31 Implemented dumping file contents
2022-04-07 Minor cleanup and add some clarifying comments.
2022-04-08 Extract strupper and uppercase into util
2022-04-08 Implement write tests with single/multiple block writes
2022-04-08 Start on commandline control of SD card frontend
2022-04-08 Add info command to show some FAT properties.
2022-04-08 Implement filling the large buffer and extend command parsing
2022-04-08 Verify written blocks contain the expected data
2022-04-09 Allow the actual buffer size to be set
    This allows to better compare the single vs multiple block writes.
2022-04-09 Extracted command infrastructure
2022-04-09 Move FAT frontend to command
2022-04-09 Extracted dump_block into util
2022-04-09 Implement writing data into file
2022-06-22 Bump numpy from 1.20.3 to 1.22.0 in /modul2/P2/py
    Bumps [numpy](https://github.com/numpy/numpy) from 1.20.3 to 1.22.0.
    - [Release notes](https://github.com/numpy/numpy/releases)
    - [Changelog](https://github.com/numpy/numpy/blob/main/doc/HOWTO_RELEASE.rst)
    - [Commits](https://github.com/numpy/numpy/compare/v1.20.3...v1.22.0)
    ---
    updated-dependencies:
2023-04-19 RQ2 archived versions
2023-04-19 RQ2 v1.0 files
2023-08-27 Place current version of RQ into repo
2023-08-27 Little FAT32 utility script to format an SD card
2023-08-27 Some work in progress
2023-08-27 Get switched frontend working again
2023-08-27 Fix Qt module
2023-08-27 Use preprocessor to enable/disable HyperRAM
2023-08-27 Fix UNIHFY config and preprocessor defs

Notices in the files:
parts and their libraries:
SparkFun-Connectors: Licensing: Creative Commons ShareAlike 4.0 International - https://creativecommons.org/licenses/by-sa/4.0
